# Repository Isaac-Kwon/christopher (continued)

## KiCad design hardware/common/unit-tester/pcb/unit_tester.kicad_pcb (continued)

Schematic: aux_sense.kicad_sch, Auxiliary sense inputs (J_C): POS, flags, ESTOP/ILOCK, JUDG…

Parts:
D153, D154, D155, D156, D157, D158, D159, D160, D161, D162, D163, D164, D165, D166, D167, D168, D169, D170, D171, D172, D173, D174, D175: 1N4148W; D_SOD-123
JP2, JP3: loop (bridged); SolderJumper-2_P1.3mm_Bridged_RoundedPad1.0x1.5mm
JP4, JP5: feed (open); SolderJumper-2_P1.3mm_Open_RoundedPad1.0x1.5mm
R153, R154, R155, R156, R157, R158, R159, R160, R161, R162, R163, R164, R165, R166, R167, R168, R169, R170, R171, R172, R173, R174, R175, R404, R405: 2.2k; R_0603_1608Metric
R253, R254, R255, R256, R257, R258, R259, R260, R261, R262, R263, R264, R265, R266, R267, R268, R269, R270, R271, R272, R273, R274, R275: 10k; R_0603_1608Metric
U63, U64, U65, U66, U67, U68: TLP291-4; SOIC-16_4.55x10.3mm_P1.27mm

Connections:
+3V3: U63.10, U63.12, U63.14, U63.16, U64.10, U64.12, U64.14, U64.16, U65.10, U65.12, U65.14, U65.16, U66.10, U66.12, U66.14, U66.16, U67.10, U67.12, U67.14, U67.16, U68.12, U68.14, U68.16; also elsewhere on the board
+24V_F: R404.1, R405.1; also elsewhere on the board
/AUX_SENSE/ESTOP_FEED: JP4.1 (A), R404.2
/AUX_SENSE/ILOCK_FEED: JP5.1 (A), R405.2
/AUX_SENSE/SNS_52: D153.1 (K), R153.2, U63.1
/AUX_SENSE/SNS_53: D154.1 (K), R154.2, U63.3
/AUX_SENSE/SNS_54: D155.1 (K), R155.2, U63.5
/AUX_SENSE/SNS_55: D156.1 (K), R156.2, U63.7
/AUX_SENSE/SNS_56: D157.1 (K), R157.2, U64.1
/AUX_SENSE/SNS_57: D158.1 (K), R158.2, U64.3
/AUX_SENSE/SNS_58: D159.1 (K), R159.2, U64.5
/AUX_SENSE/SNS_59: D160.1 (K), R160.2, U64.7
/AUX_SENSE/SNS_60: D161.1 (K), R161.2, U65.1
/AUX_SENSE/SNS_61: D162.1 (K), R162.2, U65.3
/AUX_SENSE/SNS_62: D163.1 (K), R163.2, U65.5
/AUX_SENSE/SNS_63: D164.1 (K), R164.2, U65.7
/AUX_SENSE/SNS_64: D165.1 (K), R165.2, U66.1
/AUX_SENSE/SNS_65: D166.1 (K), R166.2, U66.3
/AUX_SENSE/SNS_66: D167.1 (K), R167.2, U66.5
/AUX_SENSE/SNS_67: D168.1 (K), R168.2, U66.7
/AUX_SENSE/SNS_68: D169.1 (K), R169.2, U67.1
/AUX_SENSE/SNS_69: D170.1 (K), R170.2, U67.3
/AUX_SENSE/SNS_70: D171.1 (K), R171.2, U67.5
/AUX_SENSE/SNS_71: D172.1 (K), R172.2, U67.7
/AUX_SENSE/SNS_72: D173.1 (K), R173.2, U68.1
/AUX_SENSE/SNS_73: D174.1 (K), R174.2, U68.3
/AUX_SENSE/SNS_74: D175.1 (K), R175.2, U68.5
AT_HOME_IN: R169.1; also elsewhere on the board
CLEAR_IN: R174.1; also elsewhere on the board
END_IN: R170.1; also elsewhere on the board
ESTOP_A: JP2.1 (A), JP4.2 (B); also elsewhere on the board
ESTOP_RET: JP2.2 (B), R171.1; also elsewhere on the board
GND_F: D153.2 (A), D154.2 (A), D155.2 (A), D156.2 (A), D157.2 (A), D158.2 (A), D159.2 (A), D160.2 (A), D161.2 (A), D162.2 (A), D163.2 (A), D164.2 (A), D165.2 (A), D166.2 (A), D167.2 (A), D168.2 (A), D169.2 (A), D170.2 (A), D171.2 (A), D172.2 (A), D173.2 (A), D174.2 (A), D175.2 (A), U63.2, U63.4, U63.6, U63.8, U64.2, U64.4, U64.6, U64.8, U65.2, U65.4, U65.6, U65.8, U66.2, U66.4, U66.6, U66.8, U67.2, U67.4, U67.6, U67.8, U68.2, U68.4, U68.6; also elsewhere on the board
GND_M: R253.2, R254.2, R255.2, R256.2, R257.2, R258.2, R259.2, R260.2, R261.2, R262.2, R263.2, R264.2, R265.2, R266.2, R267.2, R268.2, R269.2, R270.2, R271.2, R272.2, R273.2, R274.2, R275.2; also elsewhere on the board
ILOCK_A: JP3.1 (A), JP5.2 (B); also elsewhere on the board
ILOCK_RET: JP3.2 (B), R172.1; also elsewhere on the board
JUDGE_IN: R173.1; also elsewhere on the board
POS0_IN: R153.1; also elsewhere on the board
POS1_IN: R154.1; also elsewhere on the board
POS2_IN: R155.1; also elsewhere on the board
POS3_IN: R156.1; also elsewhere on the board
POS4_IN: R157.1; also elsewhere on the board
POS5_IN: R158.1; also elsewhere on the board
POS6_IN: R159.1; also elsewhere on the board
POS7_IN: R160.1; also elsewhere on the board
POS8_IN: R161.1; also elsewhere on the board
POS9_IN: R162.1; also elsewhere on the board
POS10_IN: R163.1; also elsewhere on the board
POS11_IN: R164.1; also elsewhere on the board
POS12_IN: R165.1; also elsewhere on the board
POS13_IN: R166.1; also elsewhere on the board
POS14_IN: R167.1; also elsewhere on the board
SENSE_52: R253.1, U63.15; also elsewhere on the board
SENSE_53: R254.1, U63.13; also elsewhere on the board
SENSE_54: R255.1, U63.11; also elsewhere on the board
SENSE_55: R256.1, U63.9; also elsewhere on the board
SENSE_56: R257.1, U64.15; also elsewhere on the board
SENSE_57: R258.1, U64.13; also elsewhere on the board
SENSE_58: R259.1, U64.11; also elsewhere on the board
SENSE_59: R260.1, U64.9; also elsewhere on the board
SENSE_60: R261.1, U65.15; also elsewhere on the board
SENSE_61: R262.1, U65.13; also elsewhere on the board
SENSE_62: R263.1, U65.11; also elsewhere on the board
SENSE_63: R264.1, U65.9; also elsewhere on the board
SENSE_64: R265.1, U66.15; also elsewhere on the board
SENSE_65: R266.1, U66.13; also elsewhere on the board
SENSE_66: R267.1, U66.11; also elsewhere on the board
SENSE_67: R268.1, U66.9; also elsewhere on the board
SENSE_68: R269.1, U67.15; also elsewhere on the board
SENSE_69: R270.1, U67.13; also elsewhere on the board
SENSE_70: R271.1, U67.11; also elsewhere on the board
SENSE_71: R272.1, U67.9; also elsewhere on the board
SENSE_72: R273.1, U68.15; also elsewhere on the board
SENSE_73: R274.1, U68.13; also elsewhere on the board
SENSE_74: R275.1, U68.11; also elsewhere on the board
STOPPED_IN: R168.1; also elsewhere on the board
STOP_LATCH_IN: R175.1; also elsewhere on the board

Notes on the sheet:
ESTOP chain (0003 4.6): the bank drives J_C 22 with its loop supply; JP2 returns it to J_C 23, which the 2.2k + opto LED senses. ILOCK chain: J_C 24 -> JP3 -> J_C 25 -> 2.2k -> opto LED. JP4 / JP5 (open) can feed a loop from +24V_F through 2.2k instead. POS/STOPPED/AT_HOME/END/JUDGE/CLEAR/STOP_LATC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

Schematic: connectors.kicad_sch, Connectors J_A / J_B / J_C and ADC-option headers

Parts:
C237: 10n 100V; C_0603_1608Metric
J1: J_A; DSUB-37_Pins_Horizontal_P2.77x2.84mm_EdgePinOffset9.90mm_Ho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
J2: J_B; DSUB-37_Pins_Horizontal_P2.77x2.84mm_EdgePinOffset9.90mm_Ho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
J3: J_C; DSUB-37_Pins_Horizontal_P2.77x2.84mm_EdgePinOffset9.90mm_Ho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
J5: ADC_OPT_MCU; PinHeader_2x06_P2.54mm_Vertical
J6: ADC_OPT_FIELD; PinHeader_2x27_P2.54mm_Vertical
R408: 1M; R_0603_1608Metric

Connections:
+3V3: J5.1; also elsewhere on the board
+24V_BANK: J3.26, J3.27; also elsewhere on the board
ADC_IN: J5.11; also elsewhere on the board
AT_HOME_IN: J3.5; also elsewhere on the board
CHASSIS_F: C237.1, J1.SH, J2.SH, J3.SH, R408.1
CLEAR_IN: J3.35; also elsewhere on the board
END_IN: J3.6; also elsewhere on the board
ESTOP_A: J3.22; also elsewhere on the board
ESTOP_RET: J3.23; also elsewhere on the board
GND_F: C237.2, J1.27, J1.28, J1.29, J2.27, J2.28, J2.29, J3.28, J3.29, J3.30, J3.31, J3.32, J3.33, J6.53, J6.54, R408.2; also elsewhere on the board
GND_M: J5.2, J5.12; also elsewhere on the board
HOME_OUT: J3.4; also elsewhere on the board
ILOCK_A: J3.24; also elsewhere on the board
ILOCK_RET: J3.25; also elsewhere on the board
JUDGE_IN: J3.34; also elsewhere on the board
MUX_EN0: J5.7; also elsewhere on the board
MUX_EN1: J5.8; also elsewhere on the board
MUX_EN2: J5.9; also elsewhere on the board
MUX_EN3: J5.10; also elsewhere on the board
MUX_S0: J5.3; also elsewhere on the board
MUX_S1: J5.4; also elsewhere on the board
MUX_S2: J5.5; also elsewhere on the board
MUX_S3: J5.6; also elsewhere on the board
NODE_0: J1.1, J6.1; also elsewhere on the board
NODE_1: J1.2, J6.2; also elsewhere on the board
NODE_2: J1.3, J6.3; also elsewhere on the board
NODE_3: J1.4, J6.4; also elsewhere on the board
NODE_4: J1.5, J6.5; also elsewhere on the board
NODE_5: J1.6, J6.6; also elsewhere on the board
NODE_6: J1.7, J6.7; also elsewhere on the board
NODE_7: J1.8, J6.8; also elsewhere on the board
NODE_8: J1.9, J6.9; also elsewhere on the board
NODE_9: J1.10, J6.10; also elsewhere on the board
NODE_10: J1.11, J6.11; also elsewhere on the board
NODE_11: J1.12, J6.12; also elsewhere on the board
NODE_12: J1.13, J6.13; also elsewhere on the board
NODE_13: J1.14, J6.14; also elsewhere on the board
NODE_14: J1.15, J6.15; also elsewhere on the board
NODE_15: J1.16, J6.16; also elsewhere on the board
NODE_16: J1.17, J6.17; also elsewhere on the board
NODE_17: J1.18, J6.18; also elsewhere on the board
NODE_18: J1.19, J6.19; also elsewhere on the board
NODE_19: J1.20, J6.20; also elsewhere on the board
NODE_20: J1.21, J6.21; also elsewhere on the board
NODE_21: J1.22, J6.22; also elsewhere on the board
NODE_22: J1.23, J6.23; also elsewhere on the board
NODE_23: J1.24, J6.24; also elsewhere on the board
NODE_24: J1.25, J6.25; also elsewhere on the board
NODE_25: J1.26, J6.26; also elsewhere on the board
NODE_26: J2.1, J6.27; also elsewhere on the board
NODE_27: J2.2, J6.28; also elsewhere on the board
NODE_28: J2.3, J6.29; also elsewhere on the board
NODE_29: J2.4, J6.30; also elsewhere on the board
NODE_30: J2.5, J6.31; also elsewhere on the board
NODE_31: J2.6, J6.32; also elsewhere on the board
NODE_32: J2.7, J6.33; also elsewhere on the board
NODE_33: J2.8, J6.34; also elsewhere on the board
NODE_34: J2.9, J6.35; also elsewhere on the board
NODE_35: J2.10, J6.36; also elsewhere on the board
NODE_36: J2.11, J6.37; also elsewhere on the board
NODE_37: J2.12, J6.38; also elsewhere on the board
NODE_38: J2.13, J6.39; also elsewhere on the board
NODE_39: J2.14, J6.40; also elsewhere on the board
NODE_40: J2.15, J6.41; also elsewhere on the board
NODE_41: J2.16, J6.42; also elsewhere on the board
NODE_42: J2.17, J6.43; also elsewhere on the board
NODE_43: J2.18, J6.44; also elsewhere on the board
NODE_44: J2.19, J6.45; also elsewhere on the board
NODE_45: J2.20, J6.46; also elsewhere on the board
NODE_46: J2.21, J6.47; also elsewhere on the board
NODE_47: J2.22, J6.48; also elsewhere on the board
NODE_48: J2.23, J6.49; also elsewhere on the board
NODE_49: J2.24, J6.50; also elsewhere on the board
NODE_50: J2.25, J6.51; also elsewhere on the board
NODE_51: J2.26, J6.52; also elsewhere on the board
POS0_IN: J3.7; also elsewhere on the board
POS1_IN: J3.8; also elsewhere on the board
POS2_IN: J3.9; also elsewhere on the board
POS3_IN: J3.10; also elsewhere on the board
POS4_IN: J3.11; also elsewhere on the board
POS5_IN: J3.12; also elsewhere on the board
POS6_IN: J3.13; also elsewhere on the board
POS7_IN: J3.14; also elsewhere on the board
POS8_IN: J3.15; also elsewhere on the board
POS9_IN: J3.16; also elsewhere on the board
POS10_IN: J3.17; also elsewhere on the board
POS11_IN: J3.18; also elsewhere on the board
POS12_IN: J3.19; also elsewhere on the board
POS13_IN: J3.20; also elsewhere on the board
POS14_IN: J3.21; also elsewhere on the board
RUN_OUT: J3.2; also elsewhere on the board
STOPPED_IN: J3.3; also elsewhere on the board
STOP_LATCH_IN: J3.36; also elsewhere on the board
STROBE_IN: J3.1; also elsewhere on the board

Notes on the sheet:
Mounting: D-sub pins at the board edge (bottom). J5/J6 are the optional analogue-sense (M5) port: the 82k/10k dividers, 4 x CD74HC4067 and the buffer live on a separate daughter board (not designed here), because a populated divider ties GND_F to GND_M and so bypasses the isolation barrier. Leave J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

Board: 4 copper layers, 458 parts (0 on the bottom side), 397 nets, no tracks yet.

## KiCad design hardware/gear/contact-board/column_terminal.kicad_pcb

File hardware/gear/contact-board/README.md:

# Contact board, column terminal and reflector card (gear bombe, track G)

Generated KiCad 10 schematics, **placement-only** PCBs (no routing: the user routes), and a column-level verification for the
scrambler column of the gear bombe. Design basis: `hardware/gear/layout.md` 3.4, `hardware/gear/concept.md` 3.1,
`hardware/gear/drum-pcb/README.md` (ring radii, pad meaning), `docs/decisions/0002-gear-detail-decisions.md` section 3 (contact),
`docs/decisions/0003-interfaces.md` 5.1-5.2 and 7 (connectors, 27-29, CHASSIS). All files are build products of the scripts.

## Parts of a column

| Design | Per column | Content |
|---|---:|---|
| `contact_board` (station) | 3 (identical) | 110 x 110, 104 Mill-Max Omniball 7845-0 contacts on the four drum rings + four 2 x 13 IDC headers J1..J4 (ring 1..4) |
| `column_terminal` | 1 | the column's `IN` / `OUT` jacks: two male D-sub 37 (pins 1-26 = wire A..Z, 27-37 **not connected**, shell = CHASSIS) + two 2 x 13 IDC ribbon headers K1 (IN), K2 (OUT) |
| `reflector_B`, `reflector_C` | 1 of them | reflector wiring card: two 2 x 13 IDC headers K1 (from the top station's ring 3), K2 (to its ring 2) joined by the reflector permutation of `data/wirings/enigma.txt` |

Column chain (layout.md 3.4 / concept.md 3.1; lower = slow drum = Enigma right rotor, upper = fast drum = left rotor):

    IN jack - lower R4 | lower R3 - middle R4 | middle R3 - upper R4 | upper R3 - reflector card - upper R2 |
    upper R1 - middle R2 | middle R1 - lower R2 | lower R1 - OUT jack

= **8 ribbons**, 26 conductors each, pin k to pin k (4 between stations, 2 to the terminal, 2 to the reflector card). Ring Rr of a
station = contacts at r = 22 / 29 / 36 / 43 mm = the drum PCB's ring r (R4/R1 = entry-side rings, R3/R2 = reflector-side rings, copy A/B).
The reflector card hangs at the top of the column (bank top edge, visible, layout.md 3.4); the terminal sits at the foot of the column
on the panel (unit-jack row, pitch 120).

## Conventions (the part that must agree with the drum PCB)

**Contact numbering.** Contact position j (0..25 = A..Z) of ring r sits at angle j x 360/26 = 13.846 deg from the index mark (A at
12 o'clock, same mark as the drum) **counter-clockwise seen from the contact (front) side**. Reason: the drum README numbers its pads
clockwise *seen from the pad side*; the contact board's front looks at that face from the other side, so the same physical order
appears counter-clockwise. Net `R<r>_<letter>` joins contact `P<r><letter>` to pin (j+1) of header J<r>. `gen_contact_pcb.py --contacts-cw`
produces the mirror image if the drum turns the other way (same open question 2 as `drum-pcb/README.md`).

**Drum-to-contact rule used by the verification.** With the drum showing letter o at the index mark, contact position g touches pad
index (g + o) mod 26. Rotor wiring W (copy A: pad 4<i> - pad 3<W[i]>, copy B: pad 1<i> - pad 2<W[i]>) then gives, for the ring-4
contact at g, the ring-3 contact at (W[g+o] - o): exactly the core's rotor map `c -> W[c+o] - o`.

**Contact footprint.** No library footprint exists, so `Christopher.pretty/Omniball_7845-0-15-20-52-14-11-0.kicad_mod` is generated:
one through-hole pad, body outline Ø4.37, ball Ø3.96, courtyard Ø4.6. **Assumed (unconfirmed, no datasheet offline):** tail hole Ø1.7,
pad Ø2.8. Neighbour gap on ring 1 is 0.95 mm body to body (layout.md); inner contact body edge r = 19.8 vs centre hole r = 19.

**Board** (`contact_board`): 110 x 110, centre hole Ø38 (index flange), posts at (+-48, +-48): two M3 holes (3.2) and two dowel holes
(3.0) on the diagonal; 4 layers (routing is the user's). Contacts on the front, ribbon headers on the **back** (flipped footprints)
in the four corners at 45 deg: R2 top left, R3 top right, R1 bottom left, R4 bottom right, so that ring 3 -> next station's ring 4
and ring 1 <- next station's ring 2 are straight ribbons up/down; pin 1 at the end nearest the board's left (R1, R2) or right (R3, R4)
edge, so all ribbons run parallel without a twist (identical header orientation on both ends, standard IDC 1:1). The header tails stand
about 2 mm proud of the front, far below the drum pad face (9 mm), outside r = 46.
**No 0 V and no CHASSIS on the station board** (decision 0003 5.2 and the board list in section 8: scrambler side); the terminal board ties shells and mounting holes
to CHASSIS only. 0003 7.1's CHASSIS-0 V RC is not needed where there is no 0 V.

## Files

| File | Purpose |
|---|---|
| `ki_common.py` | shared generator/checker library (identical copy in `hardware/common/diagonal-board` and `patch-panel`) |
| `gen_contact.py` | footprint library + four schematics (`contact_board`, `column_terminal`, `reflector_B`, `reflector_C`) |
| `gen_contact_pcb.py` | placement of the four boards (netlist from the schematic via kicad-cli) |
| `verify_contact.py` | ERC + netlist checks + negative tests |
| `verify_contact_pcb.py` | board vs schematic, DRC, geometry from the board file, negative tests |
| `verify_column.py` | composes a whole column from the board files and checks it against the Enigma scrambler |
| `Christopher.pretty/`, `fp-lib-table` | generated Omniball footprint, project footprint library |

Regenerate and verify (KiCad 10 at `C:/Program Files/KiCad/10.0`, or set `KICAD_SHARE` / `KICAD_CLI`):

    python gen_contact.py && python gen_contact_pcb.py
    python verify_contact.py && python verify_contact_pcb.py
    "%LOCALAPPDATA%/christopher/venv/Scripts/python.exe" verify_column.py [--exhaustive II-IV-V | ALL]

Build output goes to `%LOCALAPPDATA%/christopher/contact-board`; nothing is written into the repository except the generated files.

## Results (KiCad 10.0.4)

| Item | Result |
|---|---|
| ERC (all severities) | contact_board 0, column_terminal 0, reflector_B 0, reflector_C 0 |
| Parts | station: 104 Omniball + 4 IDC headers (+ 4 board holes, not in the schematic); terminal: 2 D-sub 37 + 2 IDC + 4 plated CHASSIS holes; card: 2 IDC (+ 4 NPTH) |
| Netlist checks | all 104 contacts on 2-pad nets (contact ring r letter j - header J r pin j+1); terminal J1/J2 pin k - K1/K2 pin k, pins 27-37 open; cards equal the reflector tables |
| Placement DRC | **0 violations**; unconnected items = ratsnest: station 104, terminal 59, card 26 (pcbnew count equals sum(pads-1)) |
| Geometry from the board file | all 104 contacts on r = 22/29/36/43 within 0.005 mm and on the 13.846 deg grid within 0.005 deg (counter-clockwise), letter = position; headers on the back with pin 1 at the expected end |
| Column vs scrambler | 60 wheel orders of I-V (reflector B) x 40 drum positions (incl. corners 0/25 of all drums): 2400/2400 identical; **exhaustive `--exhaustive ALL`: all 60 orders x all 17,576 positions = 1,054,560/1,054,560 identical** (about 15 min); model vs `Bombe.trace` (one-edge menu, Rust core): 72/72 identical |
| Negative tests | netlists: swapped header/terminal/card pins, wrong card: detected; PCB: swapped header pad nets, a contact moved 1 mm, moved 0.5 mm radially: detected; column: mirrored board, swapped ribbon pins (3 ribbons), reflector C instead of B, reversed drum offsets, OUT ribbon on the wrong ring: detected |

Note on the reflector card: exchanging its two ribbons (ring 2 <-> ring 3) is *not* a fault - the reflector is an involution, so
ring3[j]-ring2[R[j]] and ring2[j]-ring3[R[j]] are the same set of connections; the card is symmetric and cannot be plugged in "wrong"
in that respect.

## Open questions / not done

1. **Omniball tail hole and pad** (assumed Ø1.7 / Ø2.8): confirm with the Mill-Max 7845-0 datasheet; check that hole and pad also keep the
   0.95 mm body gap on ring 1 and the pad at r = 20.6 clear of the Ø38 hole (1.6 mm now).
2. **Contact rotation sense** (counter-clockwise on the front) rests on the drum README's "letters clockwise seen from the pad side".
   If the mechanical design turns the drum the other way, regenerate with `--contacts-cw`; `verify_column.py` must then read the board as mirrored
   (its "board mirrored" negative test shows what a wrong sense does: every case fails).
3. **Reflector card is a 2-header card.** concept.md 3.1 says "26-pin header"; a card joining ring 3 to ring 2 needs 52 terminals, so two
   2 x 13 headers (ribbons) are used. Thin reflectors (B-THIN, C-THIN) for the M4 are a one-line addition (`reflector_sheet("B-THIN")`), not generated.
   The cards are placed only (routing = permutation, 26 nets).
4. **Terminal placement/size** (116 x 62) is a proposal; the real unit-jack row (pitch 120, jacks stacked IN above OUT) and the length
   of the 26-way ribbons (stations to the panel) are mechanical design. No panel cut-out drawing yet.
5. Header orientation (ribbon polarity) is given by the pin-1 rule above; check with the real IDC sockets that "same orientation on both
   ends" gives pin n - pin n for the 45 deg corner mounting.
6. Header height versus the 16.4 mm post and ribbon bend radius, back clearance of the vertical IDC headers (9.95 mm courtyard in the corner): mechanical check.
7. Contact-board CHASSIS: mounting holes are bare (non-plated); if the posts should bond to the frame (PE) a plated variant is a one-line change.
8. Routing: 104 nets from the rings to the corner headers (4 layers reserved); user task.

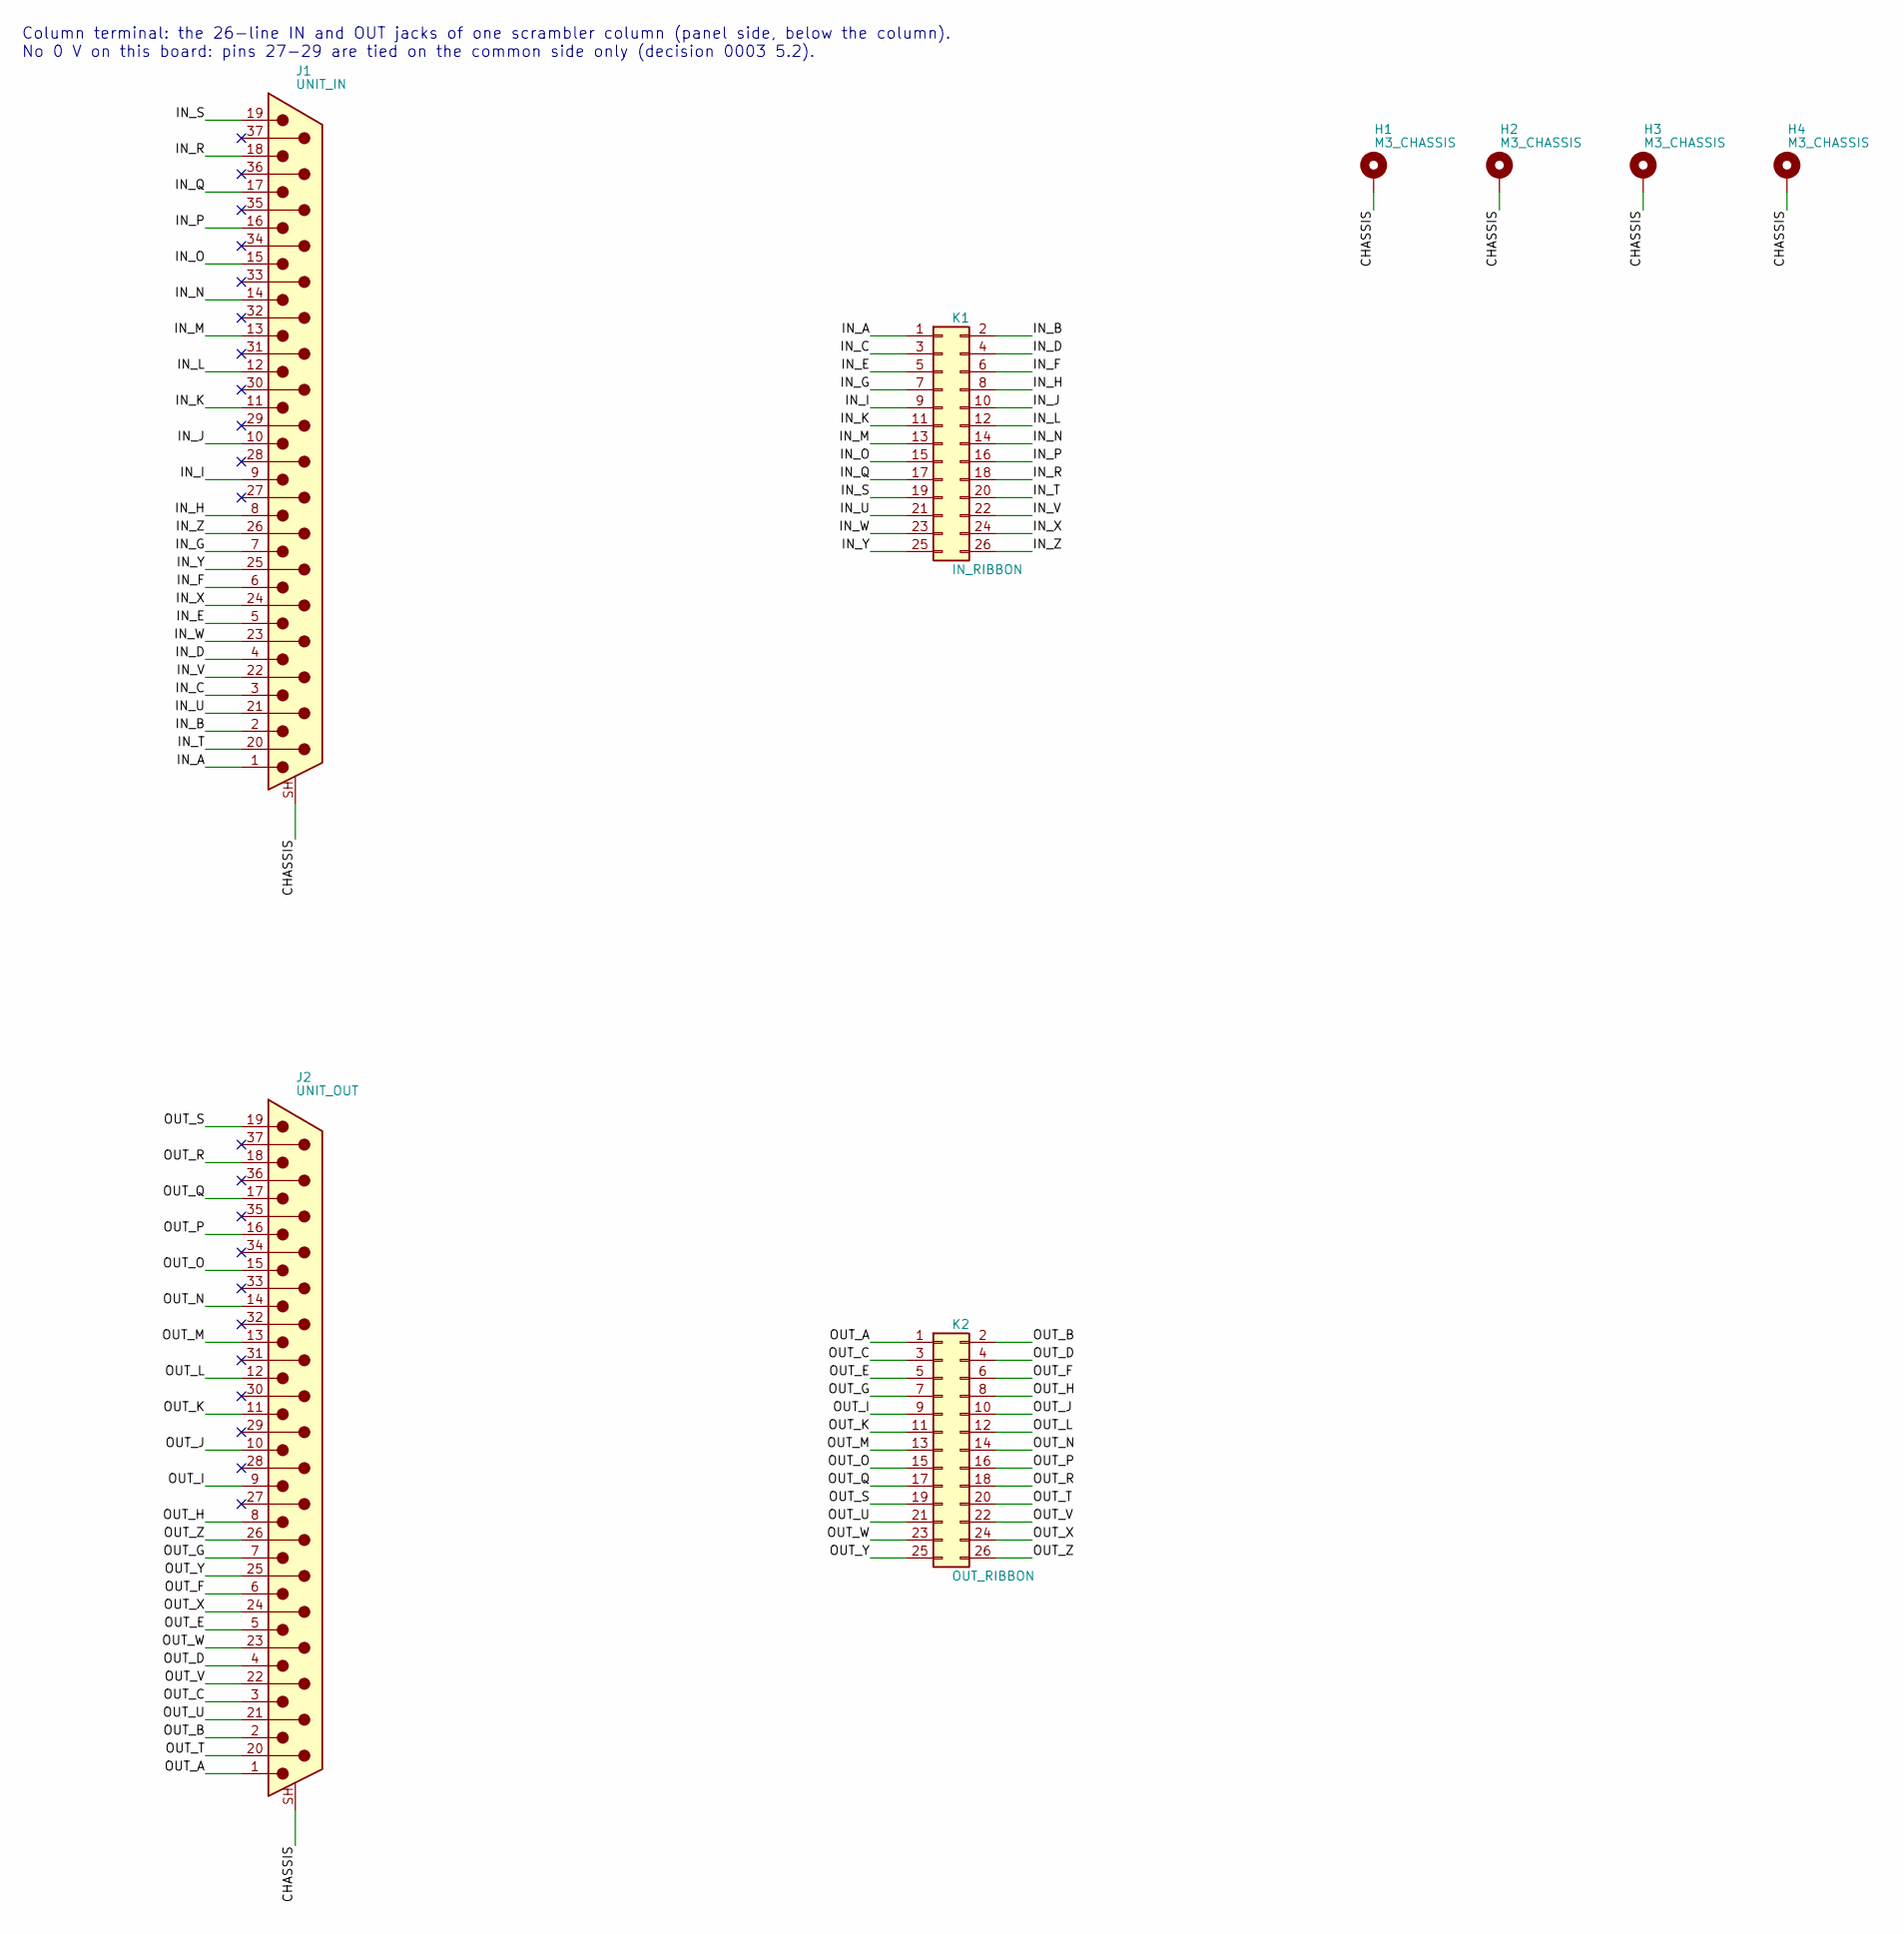
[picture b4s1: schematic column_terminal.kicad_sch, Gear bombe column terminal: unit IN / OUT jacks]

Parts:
H1, H2, H3, H4: M3_CHASSIS; MountingHole_3.2mm_M3_Pad
J1: UNIT_IN; DSUB-37_Pins_Vertical_P2.77x2.84mm_MountingHoles
J2: UNIT_OUT; DSUB-37_Pins_Vertical_P2.77x2.84mm_MountingHoles
K1: IN_RIBBON; IDC-Header_2x13_P2.54mm_Vertical
K2: OUT_RIBBON; IDC-Header_2x13_P2.54mm_Vertical

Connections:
/CHASSIS: H1.1, H2.1, H3.1, H4.1, J1.SH (PAD), J2.SH (PAD)
/IN_A: J1.1, K1.1
/IN_B: J1.2, K1.2
/IN_C: J1.3, K1.3
/IN_D: J1.4, K1.4
/IN_E: J1.5, K1.5
/IN_F: J1.6, K1.6
/IN_G: J1.7, K1.7
/IN_H: J1.8, K1.8
/IN_I: J1.9, K1.9
/IN_J: J1.10, K1.10
/IN_K: J1.11, K1.11
/IN_L: J1.12, K1.12
/IN_M: J1.13, K1.13
/IN_N: J1.14, K1.14
/IN_O: J1.15, K1.15
/IN_P: J1.16, K1.16
/IN_Q: J1.17, K1.17
/IN_R: J1.18, K1.18
/IN_S: J1.19, K1.19
/IN_T: J1.20, K1.20
/IN_U: J1.21, K1.21
/IN_V: J1.22, K1.22
/IN_W: J1.23, K1.23
/IN_X: J1.24, K1.24
/IN_Y: J1.25, K1.25
/IN_Z: J1.26, K1.26
/OUT_A: J2.1, K2.1
/OUT_B: J2.2, K2.2
/OUT_C: J2.3, K2.3
/OUT_D: J2.4, K2.4
/OUT_E: J2.5, K2.5
/OUT_F: J2.6, K2.6
/OUT_G: J2.7, K2.7
/OUT_H: J2.8, K2.8
/OUT_I: J2.9, K2.9
/OUT_J: J2.10, K2.10
/OUT_K: J2.11, K2.11
/OUT_L: J2.12, K2.12
/OUT_M: J2.13, K2.13
/OUT_N: J2.14, K2.14
/OUT_O: J2.15, K2.15
/OUT_P: J2.16, K2.16
/OUT_Q: J2.17, K2.17
/OUT_R: J2.18, K2.18
/OUT_S: J2.19, K2.19
/OUT_T: J2.20, K2.20
/OUT_U: J2.21, K2.21
/OUT_V: J2.22, K2.22
/OUT_W: J2.23, K2.23
/OUT_X: J2.24, K2.24
/OUT_Y: J2.25, K2.25
/OUT_Z: J2.26, K2.26

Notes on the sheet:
Column terminal: the 26-line IN and OUT jacks of one scrambler column (panel side, below the column). No 0 V on this board: pins 27-29 are tied on the common side only (decision 0003 5.2).

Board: 4 copper layers, 8 parts (2 on the bottom side), 53 nets, no tracks yet.

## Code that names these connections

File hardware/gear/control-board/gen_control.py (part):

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
# ----------------------------------------------------------------------------- spec tables
# Pico GPIO -> net (the pin map also used by the firmware model and checked by verify_control.py)
PICO_GPIO = {0: "PUL_M", 1: "DIR_M", 2: "ENA_M", 3: "TXEN", 4: "HOMING", 5: "SCK_M", 6: "MOSI_M", 7: "RCLK_M",
             8: "OE_M", 9: "RUN_M", 10: "STOPL_M", 11: "HOME_M", 12: "V48_M", 13: "ALM_M", 14: "SW_M",
             15: "ESTOPOK_M", 16: "ILOCKOK_M", 17: "SLOT_S", 18: "SLOT_J", 19: "SLOT_C", 20: "T_L", 21: "I_L",
             22: "T_M", 26: "I_M", 27: "T_S", 28: "I_S"}
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            14: 19, 15: 20, 16: 21, 17: 22, 18: 24, 19: 25, 20: 26, 21: 27, 22: 29, 26: 31, 27: 32, 28: 34}

# 24 V inputs: (name, net seen at the board edge, source)
INPUTS = [("RUN", "RUN", "J_CTRL pin 2"), ("STOP_LATCH", "STOP_LATCH", "J_CTRL pin 36"),
          ("HOME", "HOME", "J_CTRL pin 4"), ("ESTOP_RET", "ESTOP_RET", "J_CTRL pin 23"),
          ("ILOCK_RET", "ILOCK_RET", "J_CTRL pin 25"), ("V48_OK", "V48_OK", "J_AUX pin 1 (KM3 auxiliary contact, 24 V level)"),
          ("SW_OK", "+24V_SW", "+24V_SW rail present"), ("ALM", "ALM_IN", "J_DRV pin 5 (drive alarm, open collector)")]
INPUT_M = ["RUN_M", "STOPL_M", "HOME_M", "ESTOPOK_M", "ILOCKOK_M", "V48_M", "SW_M", "ALM_M"]

# J_CTRL (decision 0003 5.2)
POS = [f"POS{k}" for k in range(15)]
JC_PINS = {1: "STROBE", 2: "RUN", 3: "STOPPED", 4: "HOME", 5: "AT_HOME", 6: "END", 22: "ESTOP_A", 23: "ESTOP_RET",
           24: "ILOCK_A", 25: "ILOCK_RET", 34: "JUDGE", 35: "CLEAR", 36: "STOP_LATCH"}
for _k in range(15):
    JC_PINS[7 + _k] = f"POS{_k}"
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             desc="Traco TSR 1-2450, 24 V -> 5 V 1 A switching regulator", ds="https://www.tracopower.com/products/tsr1.pdf")
    cap(sh, 420, 160, "C3", "22u 10V", FP["c1206"], G("+5V"), G("GND"), "5 V rail")
    cap(sh, 460, 160, "C4", "100n", FP["c0603"], G("+5V"), G("GND"), "5 V rail HF")
    sh.place(S_DS, 520, 160, "D4", "SS14", FP["d123"], {"1": G("VSYS"), "2": G("+5V")}, rotation=0,
             desc="Schottky: +5 V -> Pico VSYS (isolates the USB supply)", show_value=False)
    cap(sh, 580, 160, "C6", "10u 10V", FP["c0805"], G("VSYS"), G("GND"), "VSYS bulk")
    for k, (rail, ref_r, ref_d, y) in enumerate([("+24V_L", "R1", "DL1", 260), ("+24V_SW", "R2", "DL2", 290),
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        nets[str(p)] = G("GND")
    nets["36"] = G("+3V3")
    nets["39"] = G("VSYS")
    nets["30"] = "RUN_PIN"
    nc += ["40", "35", "37", "33"]      # VBUS, ADC_VREF, 3V3_EN, AGND
    sh.place(S_PICO, 200, 200, "U1", "Raspberry Pi Pico", FP["pico"], nets, nc=nc,
             desc="Raspberry Pi Pico / Pico 2 module (40-pin DIP footprint). USB only for programming (VBUS unconnected: powered from VSYS)",
             ds="https://datasheets.raspberrypi.com/pico/pico-datasheet.pdf")
    sh.place(S_SW, 80, 120, "SW1", "RESET", FP["sw"], {"1": "RUN_PIN", "2": G("GND")}, desc="Reset button (RUN pin to ground)")
    cap(sh, 100, 280, "C10", "10u", FP["c0805"], G("+3V3"), G("GND"), "3.3 V bulk")
    cap(sh, 140, 280, "C11", "100n", FP["c0603"], G("+3V3"), G("GND"), "3.3 V HF")
    res(sh, 300, 120, "R10", "10k", FP["r0603"], G("TXEN"), G("GND"), desc="TXEN pull-down: no timing outputs while the Pico boots", show=True)
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
def sheet_conn() -> Sheet:
    sh = Sheet("connectors", "Connectors: J_CTRL (control connector, decision 0003 5.2), J_SAFE, J_DRV, J_AUX, test header",
               ["J_CTRL D-sub 37 PINS (male; the cable is socket-socket): 1 STROBE 2 RUN 3 STOPPED 4 HOME 5 AT_HOME 6 END 7-21 POS0-14 22-25 safety loops 28-33 0 V 34 JUDGE 35 CLEAR 36 STOP_LATCH",
                "Safety loops are bank-owned: J_SAFE feeds ESTOP_A / ILOCK_A to J_CTRL 22 / 24 and returns 23 / 25 to the safety relays K_E / K_I of the power unit",
                "Shell pads (SH) and mounting holes = CHASSIS"])
    nets = {str(p): G(JC_PINS[p]) for p in range(1, 38) if p in JC_PINS}
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
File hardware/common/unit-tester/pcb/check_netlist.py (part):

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  4. the isolation domains: no net may touch both the FIELD and the MCU domain (only the isolators and
     optocouplers may straddle), passives never bridge domains;
  5. spare / aux bits (POS, flags, JUDGE, CLEAR, STOP_LATCH) reach the HAL bit positions;
  6. decision 0003 items T1-T4, T7, T8: pin connectors, resettable fuses on RUN/HOME, ESTOP/ILOCK loops
     returned by jumpers, STOP_LATCH on 165 bit 74, CHASSIS_F pair, series P-MOSFET at the power input.

    python check_netlist.py [--netlist nl.xml] [--bom] [--selftest]
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                  f"T3: {feed} (default open) feeds {a} from +24V_F through {fr} 2.2k")
        rep.check(not any(r.startswith("R") and nl.comp[r]["value"] == "2.2k" and nl.other_pin(r, p) == "+24V_F"
                          for r, p in nl.pins_on(a)), sec, f"T3: {a} is not fed from +24V_F without the (open) jumper")
    # T4: STOP_LATCH on J_C 36 -> 2.2k -> optocoupler -> 165 bit 74; pin 37 reserved
    rep.check(nl.net("J3", "36") == "STOP_LATCH_IN" and nl.net("J3", "37").startswith("unconnected"), sec,
              "T4: J_C 36 = STOP_LATCH_IN, 37 reserved")
    # T7: CHASSIS_F pair (the shells are footprint pads SH and have no schematic pin; gen_pcb.py puts them on this net)
    members = sorted(nl.pins_on("CHASSIS_F"))
    rep.check(members == [("C237", "1"), ("R408", "1")] and nl.net("R408", "2") == "GND_F" and nl.net("C237", "2") == "GND_F"
              and nl.comp["R408"]["value"] == "1M" and nl.comp["C237"]["value"].startswith("10n"), sec,
              f"T7: CHASSIS_F joined to GND_F by R408 1M || C237 10n only (members {members})")
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        if not m:
            raise SystemExit(f"hal_pico.py: cannot find {name}")
        exp[name] = int(m[1])
    pin(r"self\.oe = machine\.Pin\((\d+)", "OE_M")
    pin(r"self\.rclk = machine\.Pin\((\d+)", "RCLK_M")
    pin(r"out_spi = machine\.SPI\(0.*?sck=machine\.Pin\((\d+)", "SCK_M")
    pin(r"out_spi = machine\.SPI\(0.*?mosi=machine\.Pin\((\d+)", "MOSI_M")
    pin(r"self\.ld = machine\.Pin\((\d+)", "LD_165")
    pin(r"in_spi = machine\.SPI\(1.*?sck=machine\.Pin\((\d+)", "SCK_165")
    pin(r"in_spi = machine\.SPI\(1.*?miso=machine\.Pin\((\d+)", "MISO_165")
    pin(r"self\.strobe = machine\.Pin\((\d+)", "STROBE_M")
    pin(r"self\.run_pin = machine\.Pin\((\d+)", "RUN_M")
    pin(r"self\.home_pin = machine\.Pin\((\d+)", "HOME_M")
    pin(r"machine\.ADC\((\d+)\)", "ADC_IN")
    m = re.search(r"self\.sel = .*? in \(([\d, ]+)\)", t)
    for i, v in enumerate(int(x) for x in m[1].split(",")):
        exp[f"MUX_S{i}"] = v
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        known = (name == "MUX_S3" and gp == 23 and where == [27])
        rep.check(known, "hal", f"{name}: HAL GP{gp} but board has {where}")
    # boot-safe: OE pulled high on the field side, RUN/HOME isolator default low
    rep.check(any(nl.comp[r]["value"] == "10k" and nl.other_pin(r, p) == "+5V_F" for r, p in nl.pins_on("OE_F") if r.startswith("R")),
              "hal", "OE_F pulled up to +5V_F")
    rep.check(nl.comp["U2"]["value"] == "ISO7340C" and nl.net("U2", "11") == "OE_F" and nl.net("U2", "6") == "OE_M",
              "hal", "OE crosses the barrier on the default-high isolator (drivers off when MCU unpowered)")
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                             ("RUN_M", "GND_M", "RUN_M pulled down"), ("HOME_M", "GND_M", "HOME_M pulled down")):
        rep.check(any(nl.comp[r]["value"] == "10k" and nl.other_pin(r, p) == other for r, p in nl.pins_on(net) if r.startswith("R")),
                  "hal", what)
    for m_net, f_net, pin_in, pin_out in (("SCK_M", "SCK_F", "3", "14"), ("MOSI_M", "MOSI_F", "4", "13"),
                                          ("RCLK_M", "RCLK_F", "5", "12"), ("OE_M", "OE_F", "6", "11")):
        rep.check(nl.net("U2", pin_in) == m_net and nl.net("U2", pin_out) == f_net, "hal", f"U2 {m_net} -> {f_net}")

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        rep.check(nl.net("J3", str(p)) == net, "conn", f"J_C pin {p} -> {net} (got {nl.net('J3', str(p))})")
    rep.check(nl.net("J3", "37").startswith("unconnected"), "conn", "J_C pin 37 reserved")
    # STROBE path
    rs = [(r, p) for r, p in nl.pins_on("STROBE_IN") if r.startswith("R")]
    rep.check(len(rs) == 1 and ("J3", "1") in nl.pins_on("STROBE_IN"), "conn", "STROBE_IN: J_C 1 -> one resistor -> 6N137")
    rep.check(nl.net("U5", "4") == "STROBE_M" and nl.net("U4", "6") == nl.net("U5", "2"), "conn", "6N137 -> inverter -> STROBE_M")


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        ("T3: ILOCK loop fed from +24V_F by default (JP5 bridged)", set_comp(nl, "JP5", fp="Jumper:SolderJumper-2_P1.3mm_Bridged_RoundedPad1.0x1.5mm")),
        ("T3: J_C 22/23 swapped (loop direction reversed)", swap_nets(nl, ("J3", "22"), ("J3", "23"))),
        ("T4: STOP_LATCH (J_C 36) and JUDGE (J_C 34) swapped", swap_nets(nl, ("J3", "36"), ("J3", "34"))),
        ("T7: CHASSIS_F resistor R408 returned to 0 V of the MCU side", move_pin(nl, ("R408", "2"), "GND_M")),
        ("T7: CHASSIS_F capacitor missing (C237 pin 1 on GND_F)", move_pin(nl, ("C237", "1"), "GND_F")),
        ("T8: reversed series P-MOSFET (Q1 pins 2 <-> 3)", swap_nets(nl, ("Q1", "2"), ("Q1", "3"))),
        ("T8: terminal J4 straight on +24V_IN (MOSFET bypassed)", move_pin(nl, ("J4", "1"), "+24V_IN")),
        ("T8: gate zener DZ1 reversed (pins 1 <-> 2)", swap_nets(nl, ("DZ1", "1"), ("DZ1", "2"))),
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
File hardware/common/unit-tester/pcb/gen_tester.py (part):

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    shift_in     10 x 74HC165 (80 bits, MCU side)
    frontend_g0..g6   one TBD62783A group: driver + 1k + 2.2k sense + TLP291-4 for 8 nodes
    aux_sense    23 auxiliary inputs (POS, STOPPED, AT_HOME, END, ESTOP, ILOCK, JUDGE, CLEAR, STOP_LATCH) + loop jumpers
    connectors   J_A, J_B, J_C (DC37 pins: decision 0003 5.1, the cables are socket-socket), CHASSIS_F pair, ADC-option headers
"""
from __future__ import annotations

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
# J_C = control connector of decision 0003 5.2.  22/24 = ESTOP_A / ILOCK_A (the bank feeds the loop), 23/25 = the
# return, sensed through 2.2k; the tester closes each loop with a solder jumper (default closed, 0003 T3).
JC_PINS = {1: "STROBE_IN", 2: "RUN_OUT", 3: "STOPPED_IN", 4: "HOME_OUT", 5: "AT_HOME_IN", 6: "END_IN",
           22: "ESTOP_A", 23: "ESTOP_RET", 24: "ILOCK_A", 25: "ILOCK_RET",
           26: "+24V_BANK", 27: "+24V_BANK", 34: "JUDGE_IN", 35: "CLEAR_IN", 36: "STOP_LATCH_IN"}
for _k in range(15):
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# Pico pin numbers by GPIO (module pinout)
PICO_PIN = {0: 1, 1: 2, 2: 4, 3: 5, 4: 6, 5: 7, 6: 9, 7: 10, 8: 11, 9: 12, 10: 14, 11: 15, 12: 16, 13: 17,
            14: 19, 15: 20, 16: 21, 17: 22, 18: 24, 19: 25, 20: 26, 21: 27, 22: 29, 26: 31, 27: 32, 28: 34}
# GPIO -> net (hal_pico.py; MUX_S3 moved GP23 -> GP27, GP23 is not on the Pico header)
PICO_NETS = {2: "STROBE_M", 3: "RUN_M", 4: "HOME_M", 6: "MUX_EN0", 7: "MUX_EN1", 8: "MUX_EN2", 9: "MUX_EN3",
             10: "SCK_165", 12: "MISO_165", 13: "LD_165", 16: "OE_M", 17: "RCLK_M", 18: "SCK_M", 19: "MOSI_M",
             20: "MUX_S0", 21: "MUX_S1", 22: "MUX_S2", 27: "MUX_S3", 26: "ADC_IN"}
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            elif num in nets:
                if key in seen:
                    if seen[key] != nets[num]:
                        raise SystemExit(f"{ref}.{num}: stacked pins with different nets {seen[key]} / {nets[num]}")
                    continue
                seen[key] = nets[num]
                self.net_at(sx, sy, o, nets[num], stub)
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
def sheet_mcu() -> Sheet:
    sh = Sheet("mcu", "MCU: Raspberry Pi Pico (RP2040) / Pico 2 (RP2350)",
               ["Pin map = firmware/hal_pico.py (one change: MUX_S3 on GP27 because GP23 is not on the Pico header)",
                "Powered from USB only; 3V3(OUT) feeds the MCU side of the isolators, the 74HC165 chain and the optocoupler outputs"])
    nets: dict[str, str] = {}
    nc = []
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    nets["36"] = G("+3V3")
    nets["39"] = G("VBUS")      # VSYS tied to VBUS (USB powered)
    nets["40"] = G("VBUS")
    nets["30"] = "RUN_PIN"
    nc += ["33", "35", "37"]   # AGND (module-internal tie to GND), ADC_VREF, 3V3_EN
    sh.place(S_PICO, 200, 200, "U1", "Raspberry Pi Pico", FP["pico"], nets, nc=nc,
             desc="Raspberry Pi Pico / Pico 2 module (40-pin DIP footprint, 2x20)",
             ds="https://datasheets.raspberrypi.com/pico/pico-datasheet.pdf")
    sh.place(S_SW, 80, 120, "SW1", "RESET", FP["sw"], {"1": "RUN_PIN", "2": G("GND_M")},
             desc="Reset button (RUN pin to ground)", rotation=0)
    cap(sh, 100, 280, "C240", "10u", FP["c0805"], G("+3V3"), G("GND_M"), "3.3 V bulk")
    cap(sh, 140, 280, "C241", "100n", FP["c0603"], G("+3V3"), G("GND_M"), "3.3 V HF")
    cap(sh, 180, 280, "C242", "10u", FP["c0805"], G("VBUS"), G("GND_M"), "USB 5 V bulk")
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             nc=("12", "11"),
             desc="4-channel digital isolator, fail-safe LOW; TI ISO7340FC. Unused inputs tied low, unused outputs open",
             ds="https://www.ti.com/lit/ds/symlink/iso7340.pdf", stub=7.62)
    # OE pull-up on the field side: wire the isolator output to OE_F through a 0-R-like label join
    res(sh, 180, 220, "R401", "10k", FP["r0603"], G("OE_F"), G("+5V_F"), desc="OE pull-up (drivers off if isolator unpowered)", show=True)
    # MCU-side defaults while the Pico GPIOs float during boot: OE high (drivers off), RUN / HOME low
    res(sh, 220, 220, "R409", "10k", FP["r0603"], G("OE_M"), G("+3V3"), desc="OE_M pull-up: drivers stay off while the Pico boots", show=True)
    res(sh, 260, 220, "R410", "10k", FP["r0603"], G("RUN_M"), G("GND_M"), desc="RUN_M pull-down while the Pico boots", show=True)
    res(sh, 300, 220, "R411", "10k", FP["r0603"], G("HOME_M"), G("GND_M"), desc="HOME_M pull-down while the Pico boots", show=True)
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        cap(sh, 80 + 40 * i, 320, ref, "100n", FP["c0603"], a, b, "Isolator supply decoupling")
    # STROBE: 24 V logic -> 2.2k -> 6N137 LED ; output pulled up, inverted
    res(sh, 380, 100, "R402", "2.2k", FP["r0603"], G("STROBE_IN"), "STB_A", desc="STROBE LED series resistor", show=True)
    sh.place(S_D, 420, 130, "D180", "1N4148W", FP["d123"], {"1": "STB_A", "2": G("GND_F")}, rotation=0,
             desc="Reverse protection for the STROBE LED")
    sh.place(S_6N137, 480, 140, "U4", "6N137", FP["dip8"],
             {"2": "STB_A", "3": G("GND_F"), "5": G("GND_M"), "6": "STROBE_N", "7": G("+3V3"), "8": G("+3V3")},
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            nets[str(p)] = G(JC_PINS[p])
    sh.place(S_DB37, 720, 250, "J3", "J_C", FP["dsub"], nets, nc=[str(p) for p in JC_NC], stub=10.16,
             desc="D-sub 37 pins (male), control port (decision 0003 5.2)")
    # 0003 T7 / 7.1, 7.2: the D-sub shells (footprint pads SH, not a symbol pin) are CHASSIS_F; the tester has no PE of
    # its own, so CHASSIS_F is tied to GND_F through 1 Mohm || 10 nF (the cable shield brings it to the machine chassis)
    res(sh, 420, 380, "R408", "1M", FP["r0603"], G("CHASSIS_F"), G("GND_F"), desc="CHASSIS_F to GND_F: static drain", show=True)
    cap(sh, 480, 380, "C237", "10n 100V", FP["c0603"], G("CHASSIS_F"), G("GND_F"), "CHASSIS_F to GND_F: ESD / HF path")
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
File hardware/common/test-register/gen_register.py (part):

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            f'\t\t\t\t)\n\t\t\t)\n\t\t)\n\t)')


# J2 (BANK) pin map = the control connector of decision 0003 5.2.  1 STROBE, 2 RUN, 3 STOPPED, 4 HOME (panel Home button,
# 0003 4.3), 22/23 ESTOP_A/B and 24/25 ILOCK_A/B (safety loops, closed here by solder jumpers, 0003 4.6), 34 JUDGE,
# 35 CLEAR, 36 STOP_LATCH (confirmed).  Not used by the register: 5 AT_HOME, 6 END, 7-21 POS, 26-27 +24V_AUX, 37 reserved.
J2_MAP = {1: "STROBE", 2: "RUN", 3: "STOPPED", 4: "HOME", 22: "ESTOP_A", 23: "ESTOP_B", 24: "ILOCK_A", 25: "ILOCK_B",
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    dsub("J1", "TEST_REG_IN", 70, 80, {i + 1: f"L_{letter(i)}" for i in range(N)}, [27, 28, 29],
         "D-sub 37 pins: 1-26 = lines A-Z from the menu panel (test register cable), 27-29 = 0 V, 30-37 reserved")
    dsub("J2", "BANK", 70, 190, J2_MAP, J2_GND,
         "D-sub 37 pins (decision 0003 control connector): 1 STROBE, 2 RUN, 3 STOPPED, 4 HOME, 22-23 ESTOP loop, 24-25 ILOCK loop, "
         "34 JUDGE, 35 CLEAR, 36 STOP_LATCH, 28-33 0 V; 5-21, 26-27, 37 not connected")
    dsub("J3", "DISPLAY", 70, 300, {**{i + 1: f"LAMP_{letter(i)}" for i in range(N)}, 27: "LAMP_STOP",
                                    28: "+24VD", 29: "+24VD", 30: "+24VD"}, [31, 32, 33, 34, 35, 36, 37],
         "D-sub 37 pins: 1-26 = LAMP_A..Z (low = display slave relay energised), 27 = LAMP_STOP, 28-30 = +24 V (fused), 31-37 = 0 V")
    sh.part(S_TB2, 70, 400, "J4", "24V_IN", FP_TB2, {"1": "VIN", "2": "GND"}, "", "Power in: 1 = +24 V, 2 = 0 V",
            length=5.08)
    sh.part(S_TB2, 70, 420, "J5", "TEST_OUT", FP_TB2, {"1": "TEST", "2": "GND"}, "",
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    sh.part(S_TB8, 70, 445, "J6", "PANEL", FP_TB8,
            {"1": "+24V", "2": "START_SW", "3": "RELEASE_SW", "4": "GND", "5": "HOME", "6": "ESTOP_A", "7": "ESTOP_B"}, "",
            "Front panel (0003 5.2): 1 = +24 V (switch common), 2 = START switch return (normally open, maintained), "
            "3 = RELEASE push-button return (normally open, 50 ms or longer), 4 = 0 V, 5 = HOME button return -> J2 pin 4, "
            "6-7 = emergency-stop button b-contact between ESTOP_A and ESTOP_B (cut SJ1 when fitted), 8 reserved", length=5.08)
    # 0003 R3: the bank-owned safety loops come back through the common part; closed by solder jumpers (cut to fit a panel button)
    sh.part(S_SJ, 150, 330, "SJ1", "ESTOP loop (bridged)", FP_SJ, {"1": "ESTOP_A", "2": "ESTOP_B"}, "",
            "Solder jumper, closed by default: returns ESTOP_A (J2 pin 22) to ESTOP_B (J2 pin 23). Cut it when an emergency-stop button is wired to J6 pins 6-7",
            show_value=False)
    sh.part(S_SJ, 150, 350, "SJ2", "ILOCK loop (bridged)", FP_SJ, {"1": "ILOCK_A", "2": "ILOCK_B"}, "",
            "Solder jumper, closed by default: returns ILOCK_A (J2 pin 24) to ILOCK_B (J2 pin 25)", show_value=False)

    # ---- power
    # 0003 R6 / 7.3: series P-channel MOSFET (drain on the supply side, so a reversed supply keeps it off; gate 12 V
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    sh.part(S_CP, 280, 400, "C2", "100u/35V", FP_CP, {"1": "+24VD", "2": "GND"}, "", "Bulk capacitor, display rail")
    sh.part(S_TVS, 310, 400, "DV1", "SMAJ33A", FP_TVS, {"1": "VMOS", "2": "GND"}, "",
            "Transient suppressor (cathode on +24 V), behind the series MOSFET", show_value=False)
    # 0003 R5 / 7.1: D-sub shells (footprint pads SH, no schematic pin) and the four plated mounting holes are CHASSIS;
    # one 1 Mohm || 10 nF/100 V between CHASSIS and 0 V.
    for k, (hx, hy) in enumerate([(340, 400), (360, 400), (380, 400), (400, 400)], 1):
        sh.part(S_HOLE, hx, hy, f"H{k}", "MountingHole_Pad", FP_HOLE, {"1": "CHASSIS"}, "",
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    sh.part(S_R, 190, 220, "RR1", "10k", FP_R, {"1": "RUN", "2": "GND"}, desc="RUN pull-down", show_value=False)
    sh.part(S_R, 230, 220, "RR2", "100k", FP_R, {"1": "START_SW", "2": "GND"}, desc="START pull-down", show_value=False)
    sh.part(S_R, 270, 220, "RR3", "100k", FP_R, {"1": "RELEASE_SW", "2": "GND"}, desc="RELEASE pull-down", show_value=False)
    sh.part(S_R, 310, 220, "RR4", "100k", FP_R, {"1": "HOME", "2": "GND"}, desc="HOME (J2 pin 4) pull-down", show_value=False)

    # ---- stop-bus MOSFET (LAMPGND) and stop lamp driver
    sh.part(S_R, 190, 270, "RS1", "33k", FP_R, {"1": "SN", "2": "SG"}, desc="Stop gate divider top", show_value=False)
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
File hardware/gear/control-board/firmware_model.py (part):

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    v_home: float = 20800.0         # HOME speed: 2 x the run speed (parameter)
    a_home: float = 8.0e5
    v_hcreep: float = 3000.0
    ret_offset: int = 10            # steps after the sensed end of CLEAR (zone CLEAR end .. next STROBE rise = 330 .. 374,
                                    # 44 steps; worst case about 20 steps with the slowest calibrated STROBE relay)
    cell: int = CELL
    period_x: int = CYCLE_X * 676   # one full period: 676 cycle-shaft revolutions = 17,576 tested positions + carry cells
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        self.need_home = True
        self.cnt = [0, 0, 0]
        self.sync = [False, False, False]
        self.kc = 0                  # cell k (0..29) inside the cycle-shaft revolution: +1 per T_L edge, = 27 at the T_M edge
        self.kc_sync = False
        self.x_ref = None            # (x of the last T_L boundary, s at that edge)
        self.stop_kind = None        # 'latch' | 'oper' | 'end'
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        self.state = "HBACK" if self._in_cycle0() else "HSEARCH"

    def _start_flush(self):
        """standing one slotted cell before home (same place in the cell): creep forward to home with HOMING = 1 and TXEN = 0;
        on_edge enables the outputs for the CLEAR slot of that cell only (HOME flush CLEAR, decision 0003 4.4)"""
        self.txen = False
        self.flushed = False
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
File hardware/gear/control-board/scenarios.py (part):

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
def scenario_end(v, nl, rep):
    res = []
    for end_pos, label in ((17575, "full run"), (675, "slice of 676 positions")):
        tag = f"END ({label})"
        p = Params(end_pos=end_pos)
        n_start = end_pos - 3                       # test order n = 26 Q + k
        q, k = divmod(n_start, 26)
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    def no_txe(c):                        # TXE gating removed: STROBE_G = SLOT_S & 1
        for ref in ("U33",):
            for pin in ("2", "5", "13"):
                if c.net(ref, pin) == "TXE":
                    c.move_pin(ref, pin, "+3V3")
    L.append(("TXE gating removed from the three AND gates", no_txe))

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
    def estop_ret(c):
        c.swap_pins(("U40", "17"), ("U40", "13"))
    L.append(("RUN and ESTOP optocoupler emitters exchanged", lambda c: c.swap_pins(("U40", "15"), ("U40", "13"))))
    L.append(("opto input resistor R20 changed to 10k", lambda c: c.comp["R20"].__setitem__("value", "10k")))
    L.append(("Pico TXEN and HOMING pins exchanged", lambda c: c.swap_pins(("U1", "5"), ("U1", "6"))))
    L.append(("cycle hold CYC reset by POR only (not by HOMING)", lambda c: c.move_pin("U37", "13", "POR_RC")))
    return L


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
